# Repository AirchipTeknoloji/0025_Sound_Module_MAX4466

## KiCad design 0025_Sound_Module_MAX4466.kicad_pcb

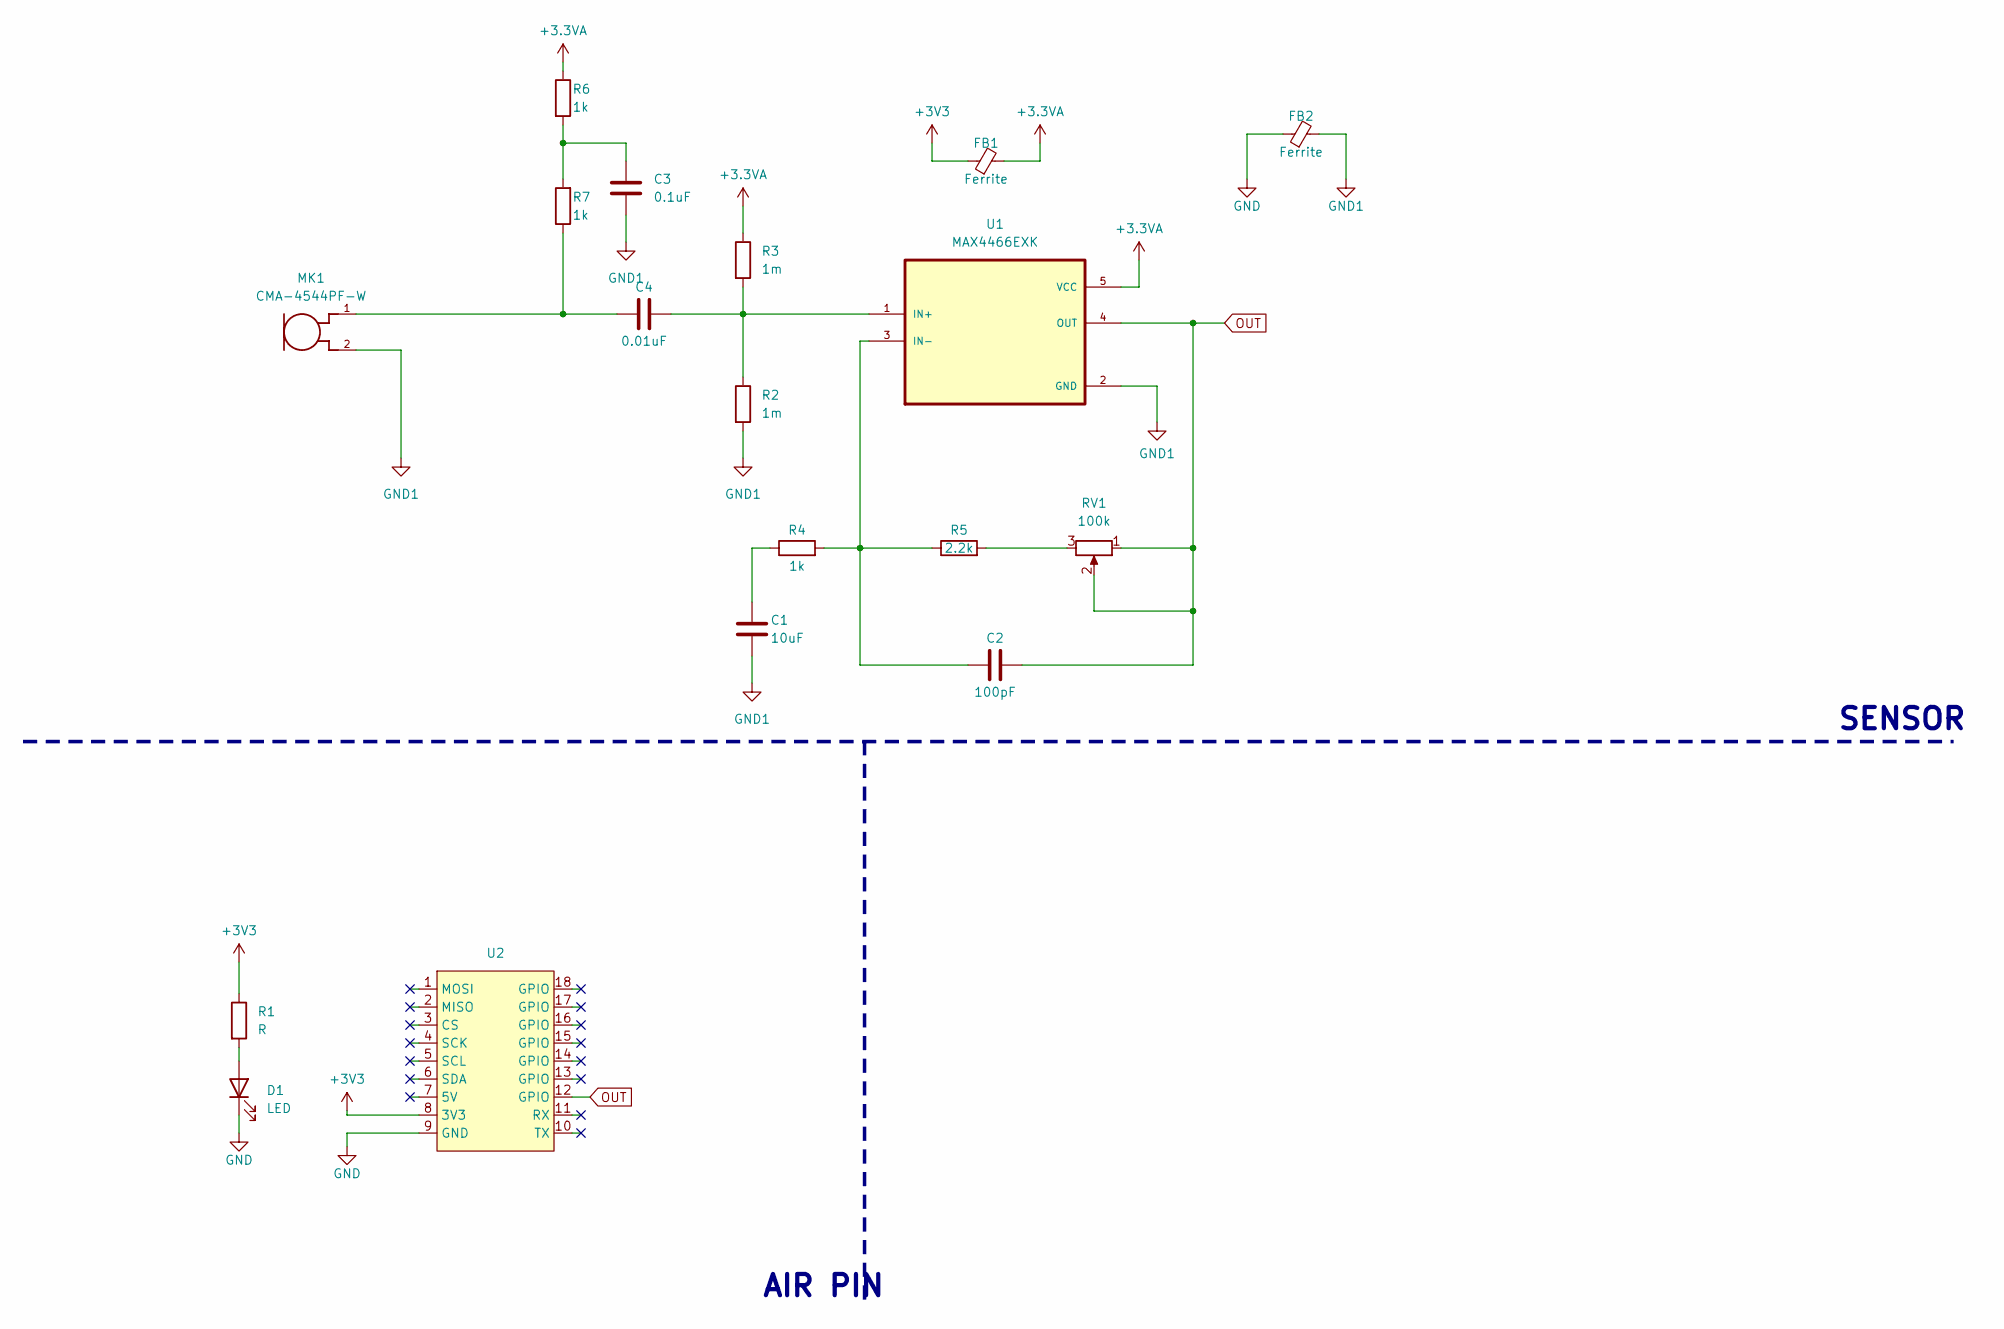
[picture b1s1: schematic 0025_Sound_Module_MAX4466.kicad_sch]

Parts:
C1: 10uF; C_0805_2012Metric
C2: 100pF; C_0805_2012Metric
C3: 0.1uF; C_0805_2012Metric
C4: 0.01uF; C_0805_2012Metric
D1: LED; LED_0805_2012Metric
FB1, FB2: Ferrite; L_0805_2012Metric
MK1: CMA-4544PF-W; MIC_CMA-4544PF-W
R1: R; R_0805_2012Metric
R2, R3: 1m; R_0805_2012Metric
R4, R6, R7: 1k; R_0805_2012Metric
R5: 2.2k; R_0805_2012Metric
RV1: 100k; 3362P_1
U1: MAX4466EXK; SOT65P210X110-5N
U2: air_module

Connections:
+3.3VA: FB1.2, R3.1, R6.1, U1.5 (VCC)
+3V3: FB1.1, R1.1, U2.8 (3V3)
GND: D1.1 (K), FB2.1, U2.9 (GND)
GND1: C1.1, C3.1, FB2.2, MK1.2, R2.2, U1.2 (GND)
unnamed: C1.2, R4.1
unnamed: C3.2, R6.2, R7.2
unnamed: C4.2, MK1.1, R7.1
unnamed: D1.2 (A), R1.2
unnamed 8: R5.2, RV1.3; also elsewhere on the board
unnamed: C4.1, R2.1, R3.2, U1.1 (IN+)
unnamed: C2.2, R4.2, R5.1, U1.3 (IN-)
OUT: C2.1, RV1.1, RV1.2, U1.4 (OUT), U2.12 (GPIO); also elsewhere on the board

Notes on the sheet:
SENSOR
AIR PIN

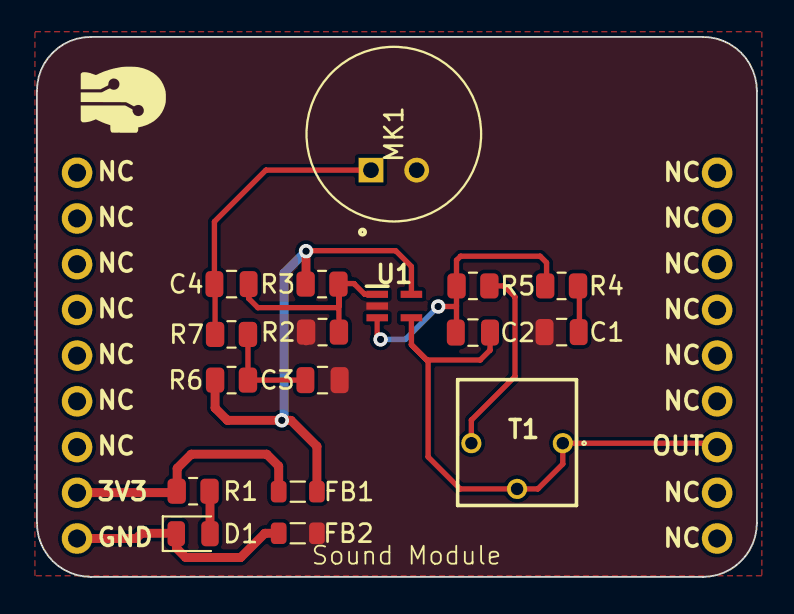
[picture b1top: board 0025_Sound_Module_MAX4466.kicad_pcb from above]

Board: 2 copper layers, 40.0 x 30.0 mm, 18 parts (0 on the bottom side), 12 nets.

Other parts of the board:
T1: R_Potentiometer; 3362P_1

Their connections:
unnamed 8: T1.3; also elsewhere on the board
OUT: T1.1, T1.2; also elsewhere on the board
